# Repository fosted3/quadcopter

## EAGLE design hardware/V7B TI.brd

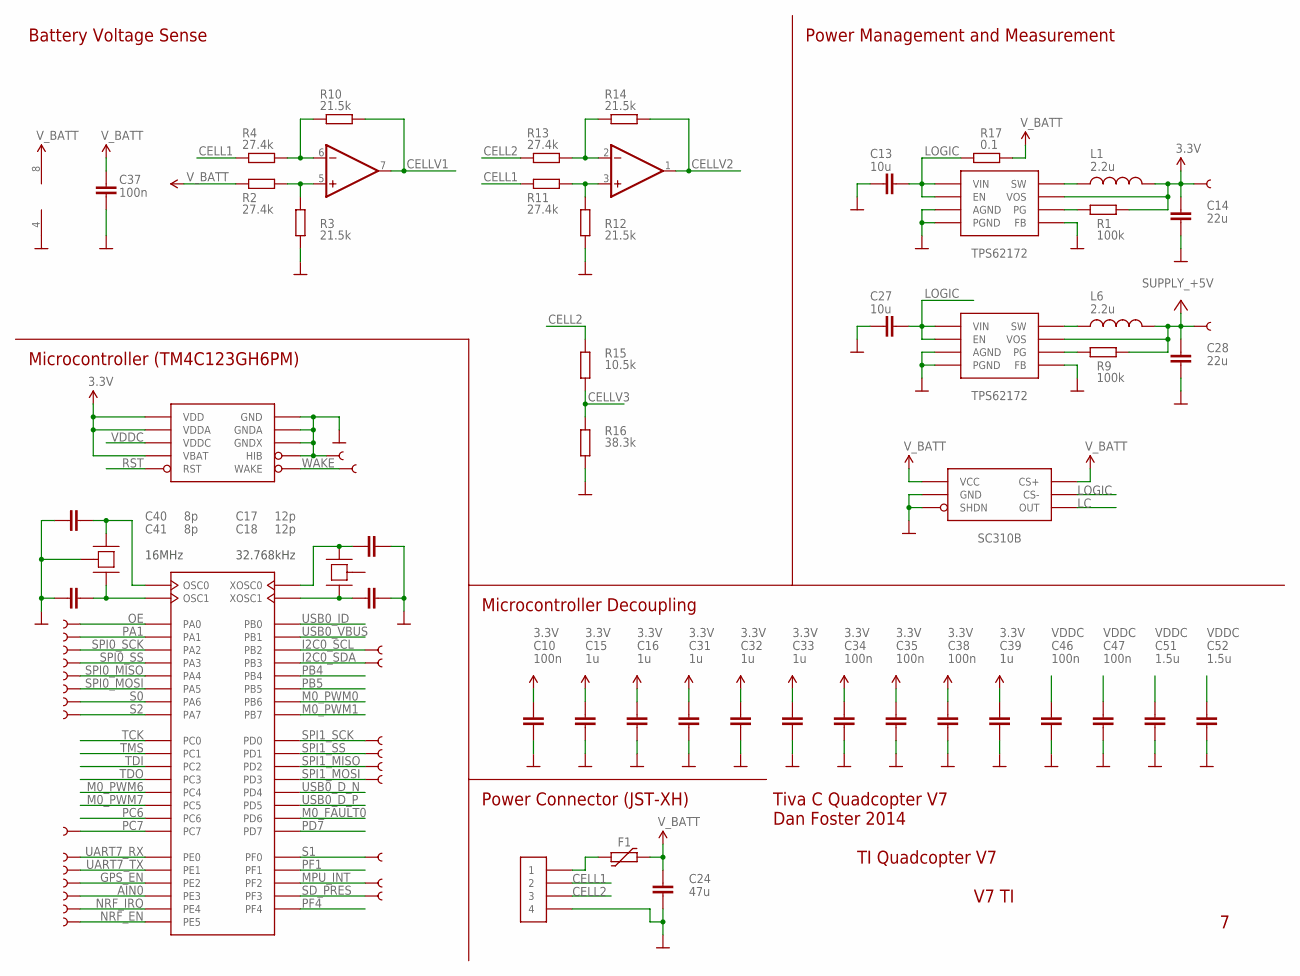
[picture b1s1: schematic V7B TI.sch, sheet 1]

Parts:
C10, C34, C35, C37, C38, C46, C47: 100n; C402
C13, C27: 10u; C805
C14, C28: 22u; C805
C15, C16, C31, C32, C33, C39: 1u; C402
C17, C18: 12p; C402
C24: 47u; C1206
C40, C41: 8p; C402
C51, C52: 1.5u; C402
F1: FUSE_PTC-1812; PTC1812L
IC2: OPA2743EA; MSOP08
L1, L6: 2.2u; 1210
R1, R9: 100k; R402
R2, R4, R11, R13: 27.4k; R402
R3, R10, R12, R14: 21.5k; R402
R15: 10.5k; R402
R16: 38.3k; R402
R17: 0.1; R1206
TP1, TP2, TP3, TP4, TP5, TP6, TP7, TP8, TP9, TP10, TP11, TP12, TP13, TP14, TP15, TP16, TP17, TP18, TP19, TP20, TP21, TP22, TP23, TP24, TP25, TP26, TP27, TP29: TEST-POINT3; PAD.03X.03
U$2, U$4: TPS62172; S-PWSON-N8
U$5: TM4C123GH6PM; TI-PM
U$6: JST-XH-4-SMD
U$7: CRYSTAL-3.2X2.5; TSX-3225
U$9: SC130; SOT-23-6
U$12: CRYSTAL-WATCH-SMD

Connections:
3.3V: C10.1, C14.2, C15.1, C16.1, C31.1, C32.1, C33.1, C34.1, C35.1, C38.1, C39.1, L1.2, R1.1, TP15.P$1, U$2.6 (VOS), U$5.P$2 (VDDA), U$5.P$11 (VDD), U$5.P$26 (VDD), U$5.P$37 (VBAT), U$5.P$42 (VDD), U$5.P$54 (VDD); also elsewhere on the board
+5V: C28.2, L6.2, R9.1, TP14.P$1, U$4.6 (VOS); also elsewhere on the board
AIN0: TP11.P$1, U$5.P$6 (PE3); also elsewhere on the board
CASE: U$12.BODY (CASE)
CELL1: R4.1, R11.1, U$6.2
CELL2: R13.1, R15.2, U$6.3
CELLV1: IC2.7 (OUT), R10.2; also elsewhere on the board
CELLV2: IC2.1 (OUT), R14.2; also elsewhere on the board
CELLV3: R15.1, R16.2; also elsewhere on the board
GND: C10.2, C13.2, C14.1, C15.2, C16.2, C17.2, C18.2, C24.2, C27.2, C28.1, C31.2, C32.2, C33.2, C34.2, C35.2, C37.2, C38.2, C39.2, C40.1, C41.1, C46.2, C47.2, C51.2, C52.2, IC2.4 (V-), R3.1, R12.1, R16.1, TP16.P$1, U$2.1 (PGND), U$2.4 (AGND), U$2.5 (FB), U$2.PAD (AGND), U$2.VIA1 (AGND), U$2.VIA2 (AGND), U$4.1 (PGND), U$4.4 (AGND), U$4.5 (FB), U$4.PAD (AGND), U$4.VIA1 (AGND), U$4.VIA2 (AGND), U$5.P$3 (GNDA), U$5.P$12 (GND), U$5.P$27 (GND), U$5.P$33 (HIB), U$5.P$35 (GNDX), U$5.P$39 (GND), U$5.P$55 (GND), U$6.4, U$7.G1 (CASE), U$7.G2 (CASE), U$9.1 (SHDN), U$9.2 (GND); also elsewhere on the board
GPS_EN: TP21.P$1, U$5.P$7 (PE2); also elsewhere on the board
I2C0_SCL: TP5.P$1, U$5.P$47 (PB2); also elsewhere on the board
I2C0_SDA: TP6.P$1, U$5.P$48 (PB3); also elsewhere on the board
LC: U$9.6 (OUT); also elsewhere on the board
LOGIC: C13.1, C27.1, R17.1, U$2.2 (VIN), U$2.3 (EN), U$4.2 (VIN), U$4.3 (EN), U$9.5 (CS-)
M0_FAULT0: U$5.P$53 (PD6)
M0_PWM0: U$5.P$1 (PB6); also elsewhere on the board
M0_PWM1: U$5.P$4 (PB7); also elsewhere on the board
M0_PWM6: U$5.P$16 (PC4); also elsewhere on the board
M0_PWM7: U$5.P$15 (PC5); also elsewhere on the board
MPU_INT: TP29.P$1, U$5.P$30 (PF2); also elsewhere on the board
unnamed: IC2.5 (+IN), R2.2, R3.2
unnamed: L1.1, U$2.7 (SW)
unnamed: C17.1, U$5.P$34 (XOSC0), U$12.2 (C2)
unnamed: R1.2, U$2.8 (PG)
unnamed: IC2.6 (-IN), R4.2, R10.1
unnamed: C18.1, U$5.P$36 (XOSC1), U$12.1 (C1)
unnamed: L6.1, U$4.7 (SW)
unnamed: R9.2, U$4.8 (PG)
unnamed: F1.1, U$6.1
unnamed: IC2.3 (+IN), R11.2, R12.2
unnamed: IC2.2 (-IN), R13.2, R14.1
unnamed: C40.2, U$5.P$40 (OSC0), U$7.C1
unnamed: C41.2, U$5.P$41 (OSC1), U$7.C2
NRF_EN: TP19.P$1, U$5.P$60 (PE5); also elsewhere on the board
NRF_IRQ: TP18.P$1, U$5.P$59 (PE4); also elsewhere on the board
OE: TP24.P$1, U$5.P$17 (PA0); also elsewhere on the board
PA1: TP25.P$1, U$5.P$18 (PA1)
PB4: U$5.P$58 (PB4)
PB5: U$5.P$57 (PB5)
PC6: U$5.P$14 (PC6)
PC7: TP27.P$1, U$5.P$13 (PC7)
PD7: U$5.P$10 (PD7)
PF1: U$5.P$29 (PF1)
PF4: U$5.P$5 (PF4)
RST: U$5.P$38 (RST); also elsewhere on the board
S0: TP12.P$1, U$5.P$23 (PA6); also elsewhere on the board
S1: TP10.P$1, U$5.P$28 (PF0); also elsewhere on the board
S2: TP13.P$1, U$5.P$24 (PA7); also elsewhere on the board
SD_PRES: TP20.P$1, U$5.P$31 (PF3); also elsewhere on the board
SPI0_MISO: TP3.P$1, U$5.P$21 (PA4); also elsewhere on the board
SPI0_MOSI: TP4.P$1, U$5.P$22 (PA5); also elsewhere on the board
SPI0_SCK: TP1.P$1, U$5.P$19 (PA2); also elsewhere on the board
SPI0_SS: TP2.P$1, U$5.P$20 (PA3); also elsewhere on the board
SPI1_MISO: TP9.P$1, U$5.P$63 (PD2); also elsewhere on the board
SPI1_MOSI: TP17.P$1, U$5.P$64 (PD3); also elsewhere on the board
SPI1_SCK: TP7.P$1, U$5.P$61 (PD0); also elsewhere on the board
SPI1_SS: TP8.P$1, U$5.P$62 (PD1); also elsewhere on the board
TCK: U$5.P$52 (PC0); also elsewhere on the board
TDI: U$5.P$50 (PC2); also elsewhere on the board
TDO: U$5.P$49 (PC3); also elsewhere on the board
TMS: U$5.P$51 (PC1); also elsewhere on the board
UART7_RX: TP23.P$1, U$5.P$9 (PE0); also elsewhere on the board
UART7_TX: TP22.P$1, U$5.P$8 (PE1); also elsewhere on the board
USB0_D_N: U$5.P$43 (PD4)
USB0_D_P: U$5.P$44 (PD5)
USB0_ID: U$5.P$45 (PB0)
USB0_VBUS: U$5.P$46 (PB1)
VDDC: C46.1, C47.1, C51.1, C52.1, U$5.P$25 (VDDC), U$5.P$56 (VDDC)
V_BATT: C24.1, C37.1, F1.2, IC2.8 (V+), R2.1, R17.2, U$9.3 (VCC), U$9.4 (CS+)
WAKE: TP26.P$1, U$5.P$32 (WAKE); also elsewhere on the board

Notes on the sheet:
Microcontroller (TM4C123GH6PM)
16MHz
32.768kHz
Power Connector (JST-XH)
TI Quadcopter V7
V7 TI
Tiva C Quadcopter V7 Dan Foster 2014
Microcontroller Decoupling
Battery Voltage Sense
Power Management and Measurement
TPS62172
SC310B

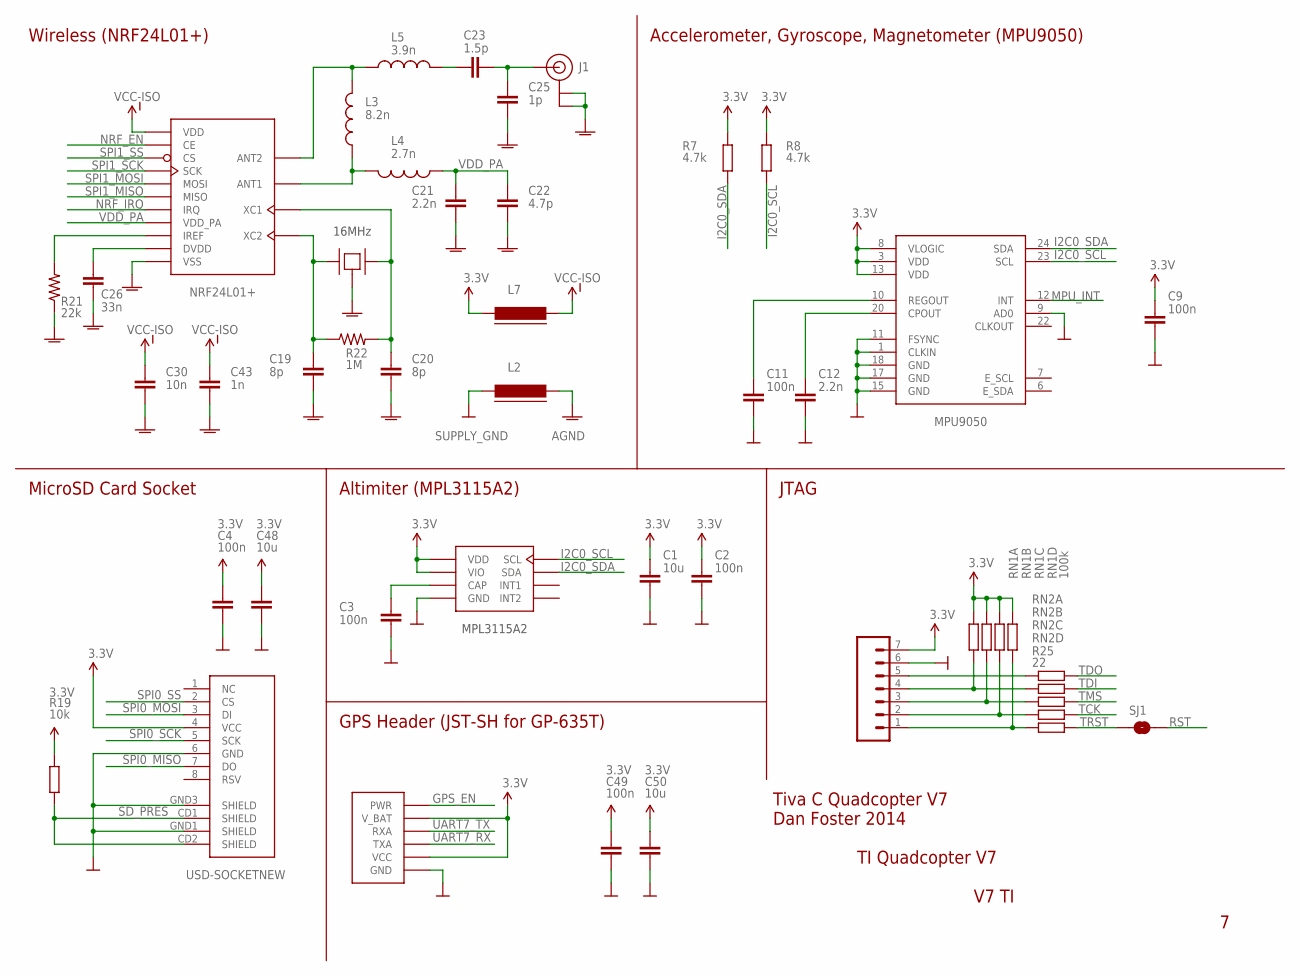
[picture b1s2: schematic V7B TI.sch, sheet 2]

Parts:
C1, C48, C50: 10u; C603
C2, C3, C4, C9, C11, C49: 100n; C402
C12: 2.2n; C402
C19, C20: 8p; 0402-CAP
C21: 2.2n; 0402-CAP
C22: 4.7p; 0402-CAP
C23: 1.5p; 0402-CAP
C25: 1p; 0402-CAP
C26: 33n; 0402-CAP
C30: 10n; 0402-CAP
C43: 1n; 0402-CAP
J1: U.FL
JP5: M07; 1X07
L2, L7: 445-8677-1-ND; FB603
L3: 8.2n; C0402
L4: 2.7n; C0402
L5: 3.9n; C0402
R7, R8: 4.7k; R402
R19: 10k; R402
R21: 22k; 0402-RES
R22: 1M; 0402-RES
R25: 22; R402
RN1: 100k; RN8P-4R-CRA06S
RN2: 22; RN8P-4R-CRA06S
SJ1: SOLDERJUMPERNO; SJ_2S-NO
U1: MPU9050; QFN-24-NP
U2: USD-SOCKETNEW; MICRO-SD-SOCKET-PP
U$3: MPL3115A2; MPLXXXXAX
U$10: GPS-GP-635T-VERT; JST-SH-6-SMD-T
U$11: NRF24L01+; QFN-20-4X4-0.5
U$13: CRYSTAL-3.2X2.5; TSX-3225

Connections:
3.3V: C1.1, C2.1, C4.1, C9.1, C48.1, C49.1, C50.1, JP5.7, L7.1, R7.1, R8.1, R19.2, RN1.5 (2), RN1.6 (2), RN1.7 (2), RN1.8 (2), U1.3 (VDD), U1.8 (VLOGIC), U1.13 (VDD), U2.4 (VCC), U$3.1 (VDD), U$3.4 (VIO), U$10.2 (VCC), U$10.5 (V_BAT); also elsewhere on the board
AGND: C19.2, C20.2, C21.2, C22.2, C25.2, C26.2, C30.2, C43.2, J1.P$1 (GND), J1.P$2 (GND), L2.2, R21.1, U$11.P$8 (VSS), U$11.P$14 (VSS), U$11.P$17 (VSS), U$11.P$20 (VSS), U$13.G1 (CASE), U$13.G2 (CASE)
GND: C1.2, C2.2, C3.2, C4.2, C9.2, C11.2, C12.2, C48.2, C49.2, C50.2, JP5.6, L2.1, U1.1 (CLKIN), U1.9 (AD0), U1.11 (FSYNC), U1.15 (GND), U1.17 (GND), U1.18 (GND), U2.6 (GND), U2.GND1 (SHIELD), U2.GND3 (SHIELD), U$3.3 (GND), U$10.1 (GND); also elsewhere on the board
GPS_EN: U$10.6 (PWR); also elsewhere on the board
I2C0_SCL: R8.2, U1.23 (SCL), U$3.8 (SCL); also elsewhere on the board
I2C0_SDA: R7.2, U1.24 (SDA), U$3.7 (SDA); also elsewhere on the board
MPU_INT: U1.12 (INT); also elsewhere on the board
unnamed: C12.1, U1.20 (CPOUT)
unnamed: C11.1, U1.10 (REGOUT)
unnamed: C19.1, R22.1, U$11.P$9 (XC2), U$13.C1
unnamed: C20.1, R22.2, U$11.P$10 (XC1), U$13.C2
unnamed: C3.1, U$3.2 (CAP)
unnamed: C23.2, C25.1, J1.P$3 (SIGNAL)
unnamed: C26.1, U$11.P$19 (DVDD)
unnamed: L3.1, L4.2, U$11.P$12 (ANT1)
unnamed: L3.2, L5.1, U$11.P$13 (ANT2)
unnamed: C23.1, L5.2
unnamed: R21.2, U$11.P$16 (IREF)
unnamed: JP5.5, RN2.1
unnamed: JP5.4, RN1.1, RN2.2 (1)
unnamed: JP5.3, RN1.2 (1), RN2.3 (1)
unnamed: JP5.2, RN1.3 (1), RN2.4 (1)
unnamed: JP5.1, R25.1, RN1.4 (1)
NRF_EN: U$11.P$1 (CE); also elsewhere on the board
NRF_IRQ: U$11.P$6 (IRQ); also elsewhere on the board
RST: SJ1.2; also elsewhere on the board
SD_PRES: R19.1, U2.CD1 (SHIELD), U2.CD2 (SHIELD); also elsewhere on the board
SPI0_MISO: U2.7 (DO); also elsewhere on the board
SPI0_MOSI: U2.3 (DI); also elsewhere on the board
SPI0_SCK: U2.5 (SCK); also elsewhere on the board
SPI0_SS: U2.2 (CS); also elsewhere on the board
SPI1_MISO: U$11.P$5 (MISO); also elsewhere on the board
SPI1_MOSI: U$11.P$4 (MOSI); also elsewhere on the board
SPI1_SCK: U$11.P$3 (SCK); also elsewhere on the board
SPI1_SS: U$11.P$2 (CS); also elsewhere on the board
TCK: RN2.5 (2); also elsewhere on the board
TDI: RN2.7 (2); also elsewhere on the board
TDO: RN2.8 (2); also elsewhere on the board
TMS: RN2.6 (2); also elsewhere on the board
TRST: R25.2, SJ1.1
UART7_RX: U$10.3 (TXA); also elsewhere on the board
UART7_TX: U$10.4 (RXA); also elsewhere on the board
VCC-ISO: C30.1, C43.1, L7.2, U$11.P$7 (VDD), U$11.P$15 (VDD), U$11.P$18 (VDD)
VDD_PA: C21.1, C22.1, L4.1, U$11.P$11 (VDD_PA)

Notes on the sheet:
16MHz
MPL3115A2
MicroSD Card Socket
Altimiter (MPL3115A2)
Wireless (NRF24L01+)
Accelerometer, Gyroscope, Magnetometer (MPU9050)
GPS Header (JST-SH for GP-635T)
JTAG
TI Quadcopter V7
V7 TI
Tiva C Quadcopter V7 Dan Foster 2014

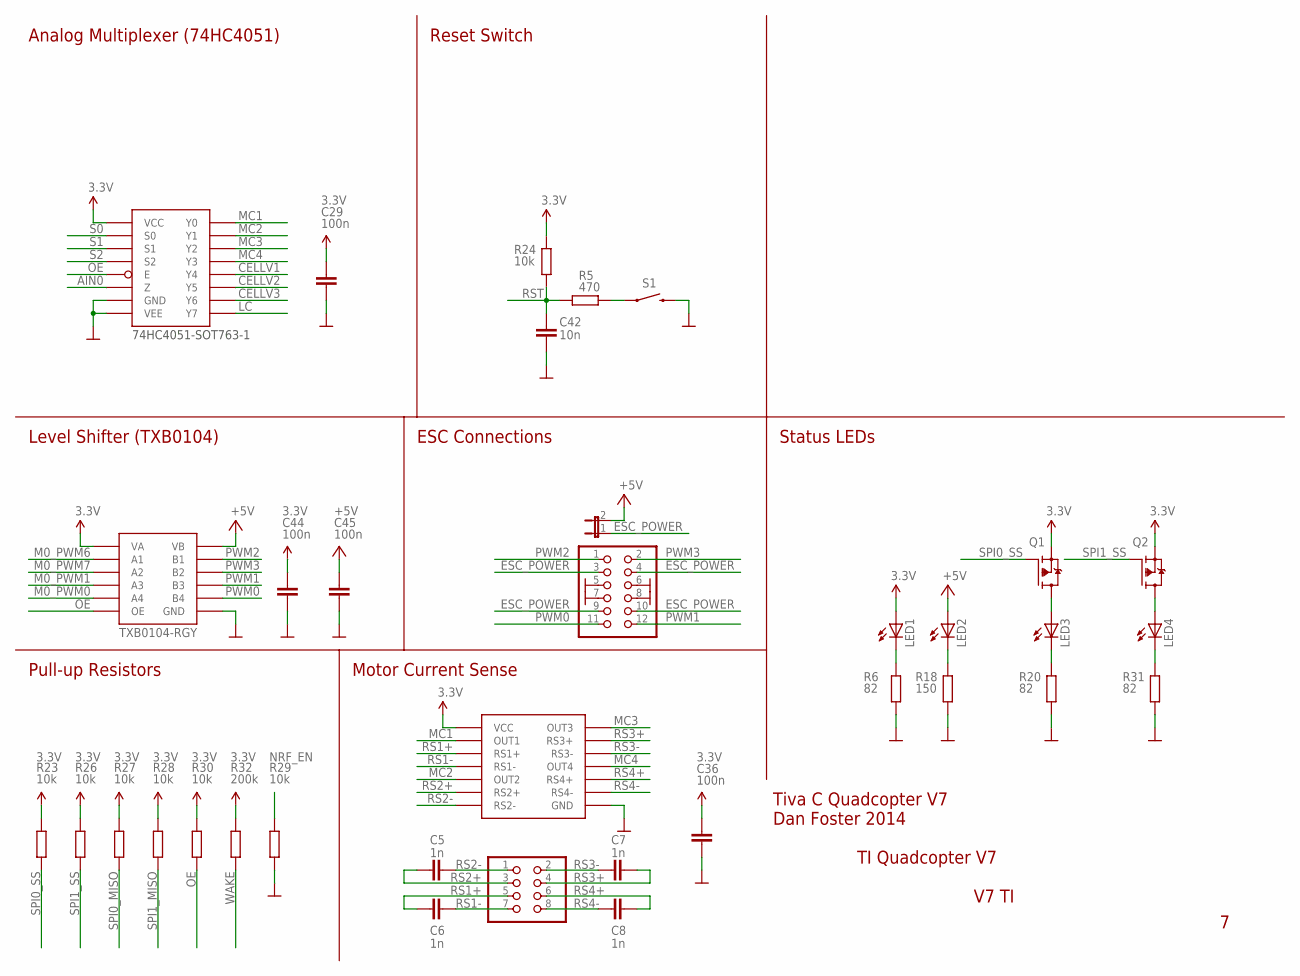
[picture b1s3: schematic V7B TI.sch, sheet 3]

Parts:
C5, C6, C7, C8: 1n; C402
C29, C36, C44, C45: 100n; C402
C42: 10n; C402
JP1: PINHD-2X6; 2X06
JP2: PINHD-2X4; 2X04
JP3: JUMPER-2SMD-NO; SJ_2S-NO
LED1, LED2, LED3, LED4: LED-0603; LED-603
Q1, Q2: BSS84CT-ND; SOT-23
R5: 470; R402
R6, R20, R31: 82; R603
R18: 150; R603
R23, R24, R26, R27, R28, R29, R30: 10k; R402
R32: 200k; R402
S1: SWITCH-MOMENTARY-2SMD; TACTILE_SWITCH_SMD
U$1: MAX4378XAUD+; TSSOP-14
U$8: 74HC4051; NXP-SOT763-1
U$18: TXB0104-RGY; TI-RGY

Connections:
3.3V: C29.1, C36.1, C44.1, LED1.A, Q1.2 (S), Q2.2 (S), R23.2, R24.2, R26.2, R27.2, R28.2, R30.2, R32.1, U$1.P$4 (VCC), U$8.16 (VCC), U$8.PAD (VCC), U$18.1 (VA); also elsewhere on the board
+5V: C45.1, JP3.2, LED2.A, U$18.14 (VB); also elsewhere on the board
AIN0: U$8.3 (Z); also elsewhere on the board
CELLV1: U$8.1 (Y4); also elsewhere on the board
CELLV2: U$8.5 (Y5); also elsewhere on the board
CELLV3: U$8.2 (Y6); also elsewhere on the board
ESC_POWER: JP1.3, JP1.4, JP1.9, JP1.10, JP3.1
GND: C29.2, C36.2, C42.2, C44.2, C45.2, JP1.5, JP1.6, JP1.7, JP1.8, R6.2, R18.2, R20.2, R29.1, R31.2, S1.3 (2), U$1.P$11 (GND), U$8.7 (VEE), U$8.8 (GND), U$18.7 (GND), U$18.PAD (GND), U$18.V1 (GND), U$18.V2 (GND), U$18.V3 (GND), U$18.V4 (GND); also elsewhere on the board
LC: U$8.4 (Y7); also elsewhere on the board
M0_PWM0: U$18.5 (A4); also elsewhere on the board
M0_PWM1: U$18.4 (A3); also elsewhere on the board
M0_PWM6: U$18.2 (A1); also elsewhere on the board
M0_PWM7: U$18.3 (A2); also elsewhere on the board
MC1: U$1.P$1 (OUT1), U$8.13 (Y0)
MC2: U$1.P$7 (OUT2), U$8.14 (Y1)
MC3: U$1.P$8 (OUT3), U$8.15 (Y2)
MC4: U$1.P$14 (OUT4), U$8.12 (Y3)
unnamed: LED1.C, R6.1
unnamed: R5.2, S1.1
unnamed: LED2.C, R18.1
unnamed: LED3.A, Q1.3 (D)
unnamed: LED3.C, R20.1
unnamed: LED4.C, R31.1
unnamed: LED4.A, Q2.3 (D)
NRF_EN: R29.2; also elsewhere on the board
OE: R30.1, U$8.6 (E), U$18.8 (OE); also elsewhere on the board
PWM0: JP1.11, U$18.10 (B4)
PWM1: JP1.12, U$18.11 (B3)
PWM2: JP1.1, U$18.13 (B1)
PWM3: JP1.2, U$18.12 (B2)
RS1+: C6.1, JP2.5, U$1.P$3 (RS1+)
RS1-: C6.2, JP2.7, U$1.P$2 (RS1-)
RS2+: C5.1, JP2.3, U$1.P$5 (RS2+)
RS2-: C5.2, JP2.1, U$1.P$6 (RS2-)
RS3+: C7.2, JP2.4, U$1.P$10 (RS3+)
RS3-: C7.1, JP2.2, U$1.P$9 (RS3-)
RS4+: C8.2, JP2.6, U$1.P$12 (RS4+)
RS4-: C8.1, JP2.8, U$1.P$13 (RS4-)
RST: C42.1, R5.1, R24.1; also elsewhere on the board
S0: U$8.11 (S0); also elsewhere on the board
S1: U$8.10 (S1); also elsewhere on the board
S2: U$8.9 (S2); also elsewhere on the board
SPI0_MISO: R27.1; also elsewhere on the board
SPI0_SS: Q1.1 (G), R23.1; also elsewhere on the board
SPI1_MISO: R28.1; also elsewhere on the board
SPI1_SS: Q2.1 (G), R26.1; also elsewhere on the board
WAKE: R32.2; also elsewhere on the board

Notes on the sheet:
Pull-up Resistors
Motor Current Sense
Level Shifter (TXB0104)
ESC Connections
Status LEDs
Reset Switch
Analog Multiplexer (74HC4051)
74HC4051-SOT763-1
TI Quadcopter V7
Tiva C Quadcopter V7 Dan Foster 2014
V7 TI

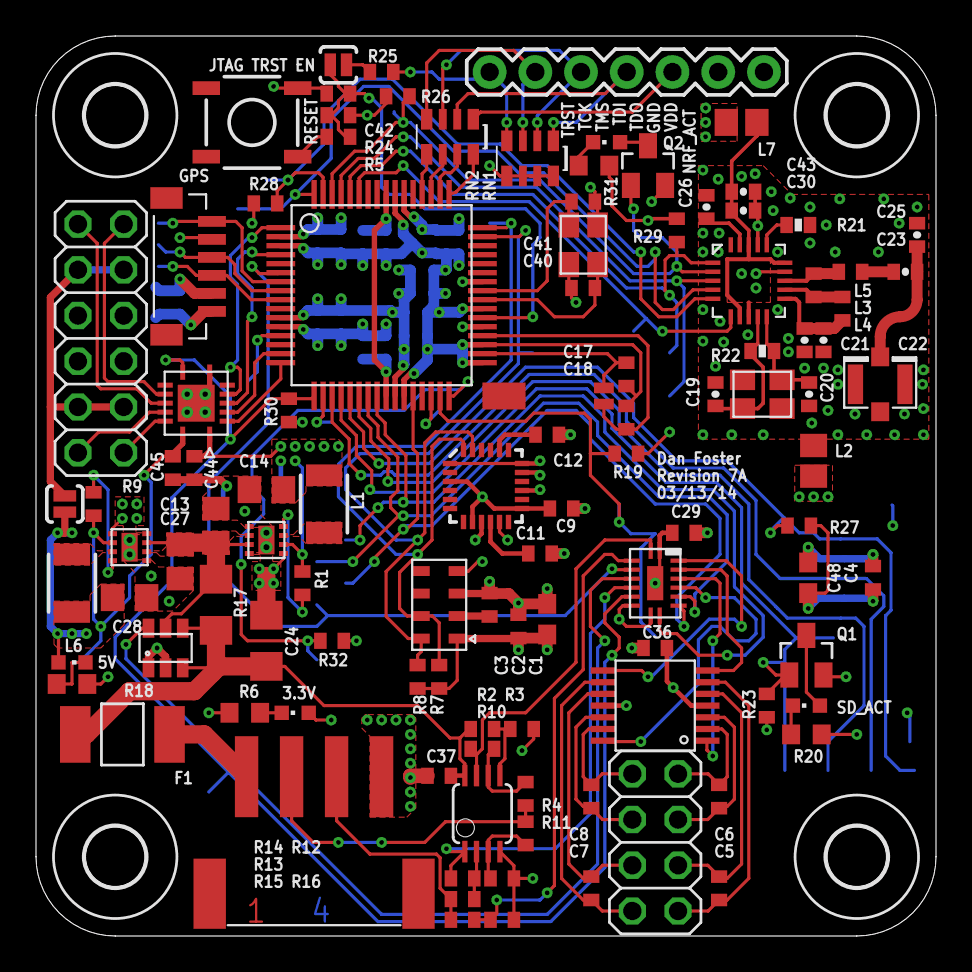
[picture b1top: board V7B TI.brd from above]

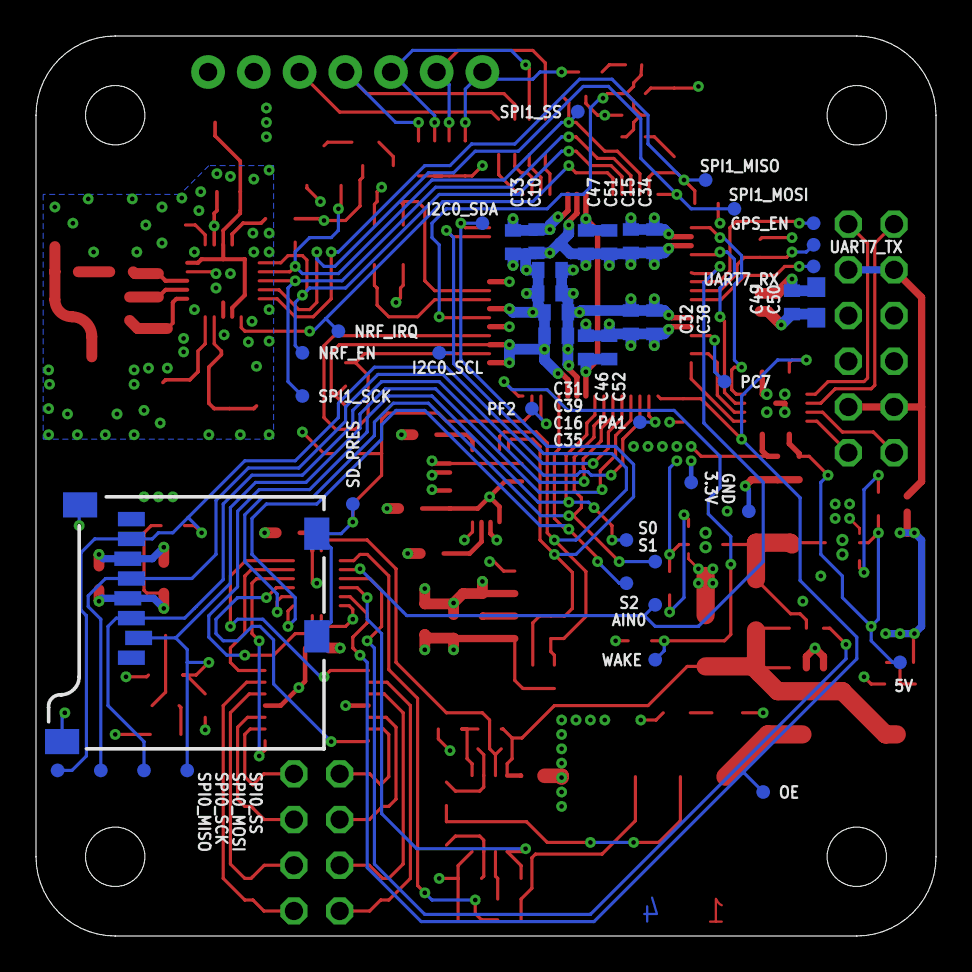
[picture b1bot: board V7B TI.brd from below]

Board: 4 copper layers, 50.0 x 50.0 mm, 156 parts (45 on the bottom side), 103 nets.

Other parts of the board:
U$19, U$20, U$21, U$22: 3,3

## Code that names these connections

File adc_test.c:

//******************************************************************************
// This program tests the ADC functionality of the board. There is a 74HC4051
// analog mux that multiplexes 8 analog signals onto AIN0 (attached to PE3)
// OE enables output, and S0:2 switch signals. OE, S0, S1, and S2 are mapped to 
// PA0, PA6, PF0, and PA7 respectively. OE is active low.
//******************************************************************************

#include <stdbool.h>
#include <stdint.h>
#include "inc/hw_memmap.h"
#include "driverlib/adc.h"
#include "driverlib/gpio.h"
#include "driverlib/pin_map.h"
#include "driverlib/sysctl.h"

void init(void)
{
	//Set system clock to 80MHz
	SysCtlClockSet(SYSCTL_SYSDIV_2_5 | SYSCTL_USE_PLL | SYSCTL_OSC_MAIN | SYSCTL_XTAL_16MHZ);
	
	//Enable ADC0, port A, port E, and port F
	SysCtlPeripheralEnable(SYSCTL_PERIPH_ADC0);
	SysCtlPeripheralEnable(SYSCTL_PERIPH_GPIOA);
	SysCtlPeripheralEnable(SYSCTL_PERIPH_GPIOE);
	SysCtlPeripheralEnable(SYSCTL_PERIPH_GPIOF);
	
	//Set A0, A6, A7, and F0 as outputs
	GPIOPinTypeGPIOOutput(GPIO_PORTA_BASE, GPIO_PIN_0 | GPIO_PIN_6 | GPIO_PIN_7);
	GPIOPinTypeGPIOOutput(GPIO_PORTF_BASE, GPIO_PIN_0);
	
	//Set E3 as AIN
	GPIOPinTypeADC(GPIO_PORTE_BASE, GPIO_PIN_3);
	
	//Setup ADC paramaters (single sample, single ended, sequence 3(?), cpu interrupt)
	ADCSequenceConfigure(ADC0_BASE, 3, ADC_TRIGGER_PROCESSOR, 0);
	ADCSequenceStepConfigure(ADC0_BASE, 3, 0, ADC_CTL_CH0 | ADC_CTL_IE | ADC_CTL_END);
	ADCSequenceEnable(ADC0_BASE, 3);
	
	//Clear interrupt
	ADCIntClear(ADC0_BASE, 3);
	
	//Write low to all outputs
	GPIOPinWrite(GPIO_PORTA_BASE, GPIO_PIN_0 | GPIO_PIN_6 | GPIO_PIN_7, 0x00);
	GPIOPinWrite(GPIO_PORTF_BASE, GPIO_PIN_0, 0x00);
}

uint32_t adc_sample(void)
{
	uint32_t val[1];
	ADCProcessorTrigger(ADC0_BASE, 3);
	while(!ADCIntStatus(ADC0_BASE, 3, false))
	{
	}
	ADCIntClear(ADC0_BASE, 3);
	ADCSequenceDataGet(ADC0_BASE, 3, val);
	return val[0];
}

uint32_t read_channel(uint32_t chan)
{
	uint32_t val;
	// S2 S1 S0
	// A7 F0 A6
	// port a
	// ((chan | 0x01) << 6) | ((chan | 0x02) << 5)
	// port f
	// ((chan | 0x04) >> 1)
	GPIOPinWrite(GPIO_PORTA_BASE, GPIO_PIN_6 | GPIO_PIN_7, ((chan | 0x01) << 6) | ((chan | 0x02) << 5));
	GPIOPinWrite(GPIO_PORTF_BASE, GPIO_PIN_0, (chan | 0x04) >> 1);
	SysCtlDelay(50); //stabilize that shit
	val = adc_sample();
	return val;
}

int main(void)
{
	init();
	uint32_t i;
	uint32_t val[8];
	for (i = 0; i < 7; i++)
	{
		val[i] = read_channel(i);
	}
}

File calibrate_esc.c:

//******************************************************************************
// This program calibrates the ESCs. ESCs should be flashed with SimonK
// firmware. Throttle is calibrated to 1060us stop, 1860us full throttle, as
// described in https://github.com/sim-/tgy/.
// ESCs are attached to PB6 (PWM 0), PB7 (PWM1), PC4 (PWM6), and PC5 (PWM7).
// OE for the level shifter is active low, and attached to PA0.
//******************************************************************************

#include <stdbool.h>
#include <stdint.h>
#include "inc/hw_memmap.h"
#include "driverlib/gpio.h"
#include "driverlib/pin_map.h"
#include "driverlib/pwm.h"
#include "driverlib/sysctl.h"

void init(void)
{
	//Set system clock to 80MHz
	SysCtlClockSet(SYSCTL_SYSDIV_2_5 | SYSCTL_USE_PLL | SYSCTL_OSC_MAIN | SYSCTL_XTAL_16MHZ);

	//Set PWM clock source to 10MHz
	SysCtlPWMClockSet(SYSCTL_PWMDIV_8);

	//Enable PWM0, port B, and port C
	SysCtlPeripheralEnable(SYSCTL_PERIPH_PWM0);
	SysCtlPeripheralEnable(SYSCTL_PERIPH_GPIOA);
	SysCtlPeripheralEnable(SYSCTL_PERIPH_GPIOB);
	SysCtlPeripheralEnable(SYSCTL_PERIPH_GPIOC);

	//Set PA0 as output for OE
	GPIOPinTypeGPIOOutput(GPIO_PORTA_BASE, GPIO_PIN_0);

	//Setup pin multiplexer
	GPIOPinConfigure(GPIO_PB6_M0PWM0);
	GPIOPinConfigure(GPIO_PB7_M0PWM1);
	GPIOPinConfigure(GPIO_PC4_M0PWM6);
	GPIOPinConfigure(GPIO_PC5_M0PWM7);

	//Set pin to PWM
	GPIOPinTypePWM(GPIO_PORTB_BASE, GPIO_PIN_6 | GPIO_PIN_7);
	GPIOPinTypePWM(GPIO_PORTC_BASE, GPIO_PIN_4 | GPIO_PIN_5);

	//Count down (left aligned), no sync
	PWMGenConfigure(PWM0_BASE, PWM_GEN_0, PWM_GEN_MODE_DOWN | PWM_GEN_MODE_NO_SYNC);
	PWMGenConfigure(PWM0_BASE, PWM_GEN_3, PWM_GEN_MODE_DOWN | PWM_GEN_MODE_NO_SYNC);

	//Set period to 4ms (Each count is 0.1us)
	PWMGenPeriodSet(PWM0_BASE, PWM_GEN_0, 40000);
	PWMGenPeriodSet(PWM0_BASE, PWM_GEN_3, 40000);

	//Set all pulse widths to 0
	PWMPulseWidthSet(PWM0_BASE, PWM_OUT_0, 0);
	PWMPulseWidthSet(PWM0_BASE, PWM_OUT_1, 0);
	PWMPulseWidthSet(PWM0_BASE, PWM_OUT_6, 0);
	PWMPulseWidthSet(PWM0_BASE, PWM_OUT_7, 0);
	
	//Enable generators 0 and 3 (controlling outputs 0, 1 and 6, 7)
	PWMGenEnable(PWM0_BASE, PWM_GEN_0);
	PWMGenEnable(PWM0_BASE, PWM_GEN_3);

	//Enable pin outputs
	PWMOutputState(PWM0_BASE, (PWM_OUT_0_BIT | PWM_OUT_1_BIT | PWM_OUT_6_BIT | PWM_OUT_7_BIT), true);

	//Bring OE line high (enables output from level shifter)
	GPIOPinWrite(GPIO_PORTA_BASE, GPIO_PIN_0, 0xFF);
	
}

int main(void)
{
	//Delay - 5 seconds (5 seconds * 80 MHz / 3)
	uint32_t delay = 133333333;
	
	//Initialize everything
	init();

	//Wait a bit
	SysCtlDelay(delay);

	//Set PWM to maximum - 1860us high
	PWMPulseWidthSet(PWM0_BASE, PWM_OUT_0, 18640);
	PWMPulseWidthSet(PWM0_BASE, PWM_OUT_1, 18640);
	PWMPulseWidthSet(PWM0_BASE, PWM_OUT_6, 18640);
	PWMPulseWidthSet(PWM0_BASE, PWM_OUT_7, 18640);

	//Wait for cal
	SysCtlDelay(delay);

	//Set PWM to minimum - 1060us high
	PWMPulseWidthSet(PWM0_BASE, PWM_OUT_0, 10600);
	PWMPulseWidthSet(PWM0_BASE, PWM_OUT_1, 10600);
	PWMPulseWidthSet(PWM0_BASE, PWM_OUT_6, 10600);
	PWMPulseWidthSet(PWM0_BASE, PWM_OUT_7, 10600);

	//Wait for cal
	SysCtlDelay(delay);

	//Disable PWM
	PWMPulseWidthSet(PWM0_BASE, PWM_OUT_0, 0);
	PWMPulseWidthSet(PWM0_BASE, PWM_OUT_1, 0);
	PWMPulseWidthSet(PWM0_BASE, PWM_OUT_6, 0);
	PWMPulseWidthSet(PWM0_BASE, PWM_OUT_7, 0);
	while (1)
	{
	}
}

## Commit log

2014-03-24 Created .gitignore
2014-03-24 Fixed files that should be ignored
2014-03-24 Added .d and .ld files to .gitignore
2014-03-24 Removed ROM calls
2014-03-24 Updated .gitignore to ignore gcc build directory
2014-03-25 Added a bunch of stuff
2014-03-25 tilib link, Makefile update
2014-03-25 debugging interface things
2014-03-25 note for dan
2014-03-25 fuck that thing
2014-03-26 changed driverlib calls to ROM_
2014-03-26 more stuff
2014-03-26 moved tilib location, spelling
2014-03-26 removed compdcm
2014-03-26 Added todo list
2014-03-26 interupt from mpu9150 needs to be brought to a gpio
2014-03-27 Started MPU9150 driver
2014-03-27 Main time
2014-03-28 Added some hardware files
2014-03-28 added buspirate jtag stuff
2014-03-28 Added a lot

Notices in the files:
parts and their libraries:
SparkFun-Sensors: Licensing: CC v3.0 Share-Alike You are welcome to use this library for commercial purposes.
SparkFun-Capacitors: Licensing: Creative Commons ShareAlike 4.0 International - https://creativecommons.org/licenses/by-sa/4.0
